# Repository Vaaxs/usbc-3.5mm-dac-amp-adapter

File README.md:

# usbc-3.5mm-dac-amp-adapter
Project for Stasis, a DAC amp that is also an adapter, to go from USB-C to 3.5mm.

## How it works

USB-C in → PCM2704CDB DAC → 3.5mm TRS out. The chip enumerates as a standard USB Audio Class device, so there is no firmware or drivers needed.

Specs

| Parameter | Value |
|---|---|
| DAC IC | Texas Instruments PCM2704CDB |
| Package | SSOP-28, 0.65mm pitch |
| USB | Full-speed USB 2.0 via USB-C receptacle |
| Output | 3.5mm TRS (stereo, no mic) |
| Sample rate | Up to 48 kHz, 16-bit |
| Crystal | 12 MHz ABM8-12.000MHZ-12-B1U-T |
| Power | Bus-powered from USB (500mA max) |
| Protection | 500mA polyfuse on VBUS |
| Board size | ~72mm × 22mm |
| Mounting | Two M2 mounting holes |

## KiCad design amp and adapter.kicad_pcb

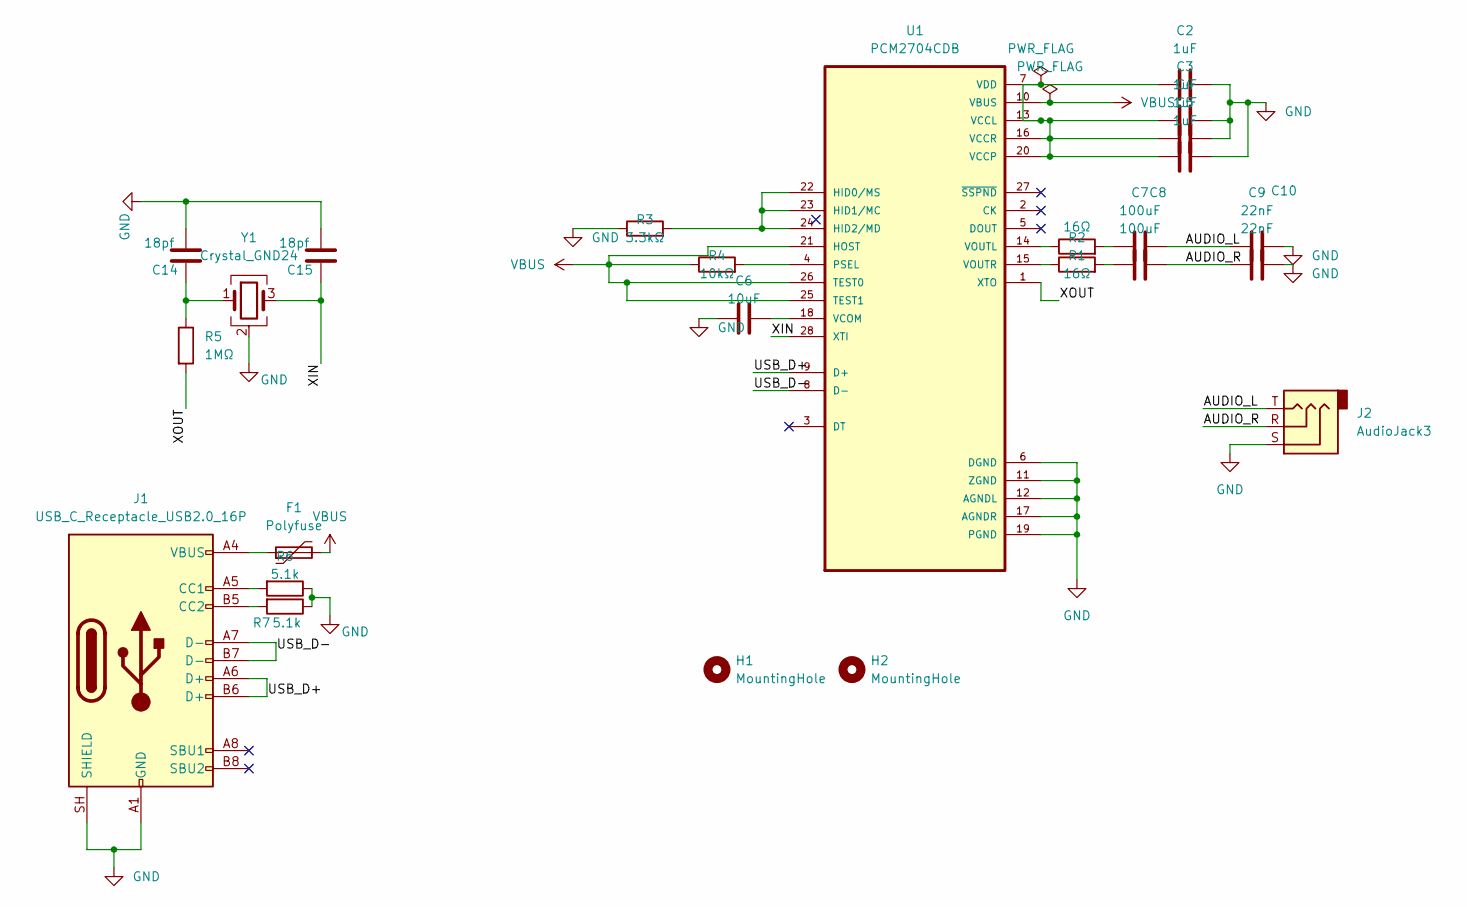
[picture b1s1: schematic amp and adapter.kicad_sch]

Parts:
C2, C3, C4, C5: 1uF; C_0402_1005Metric; LCSC Part # C52923
C6: 10uF; C_0805_2012Metric; LCSC Part # C15850
C7, C8: 100uF; C_1210_3225Metric; LCSC Part # C15008
C9, C10: 22nF; C_0402_1005Metric; LCSC Part # C1534
C14, C15: 18pf; C_0402_1005Metric; LCSC Part # C1548
F1: Polyfuse; Fuse_0805_2012Metric; LCSC Part # C70077
H1, H2: MountingHole; MountingHole_2.2mm_M2
J1: USB_C_Receptacle_USB2.0_16P; USB_C_Receptacle_HRO_TYPE-C-31-M-12; LCSC Part # C165948
J2: AudioJack3; Jack_3.5mm_CUI_SJ-3523-SMT_Horizontal; LCSC Part # C4991872
R1, R2: 16Ω; R_0402_1005Metric; LCSC Part # C25095
R3: 3.3kΩ; R_0402_1005Metric; LCSC Part # C25890
R4: 10kΩ; R_0402_1005Metric; LCSC Part # C25744
R5: 1MΩ; R_0402_1005Metric; LCSC Part # C26083
R6, R7: 5.1k; R_0402_1005Metric
U1: PCM2704CDB; SOP65P780X200-28N; LCSC Part # C5964
Y1: Crystal_GND24; Crystal_SMD_3225-4Pin_3.2x2.5mm; LCSC Part # C9002

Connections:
/AUDIO_L: C7.2, C9.2, J2.T
/AUDIO_R: C8.2, C10.2, J2.R
/USB_D+: J1.A6 (D+), J1.B6 (D+), U1.9 (D+)
/USB_D-: J1.A7 (D-), J1.B7 (D-), U1.8 (D-)
/XIN: C15.1, U1.28 (XTI), Y1.3
/XOUT: R5.2, U1.1 (XTO)
GND: C2.2, C3.2, C4.2, C5.2, C6.1, C9.1, C10.1, C14.2, C15.2, J1.A1 (GND), J1.A12 (GND), J1.B1 (GND), J1.B12 (GND), J1.SH (SHIELD), J2.S, R3.1, R6.1, R7.1, U1.6 (DGND), U1.11 (ZGND), U1.12 (AGNDL), U1.17 (AGNDR), U1.19 (PGND), Y1.2 (G), Y1.4 (G)
unnamed: C7.1, R2.2
unnamed: C8.1, R1.2
unnamed: C14.1, R5.1, Y1.1
unnamed: F1.1, J1.A4 (VBUS), J1.A9 (VBUS), J1.B4 (VBUS), J1.B9 (VBUS)
unnamed: J1.A5 (CC1), R6.2
unnamed: J1.B5 (CC2), R7.2
unnamed: R3.2, U1.22 (HID0/MS), U1.23 (HID1/MC), U1.24 (HID2/MD)
unnamed: R4.2, U1.4 (PSEL)
unnamed: C2.1, C3.1, C4.1, C5.1, U1.7 (VDD), U1.13 (VCCL), U1.16 (VCCR), U1.20 (VCCP)
unnamed: C6.2, U1.18 (VCOM)
unnamed: R2.1, U1.14 (VOUTL)
unnamed: R1.1, U1.15 (VOUTR)

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
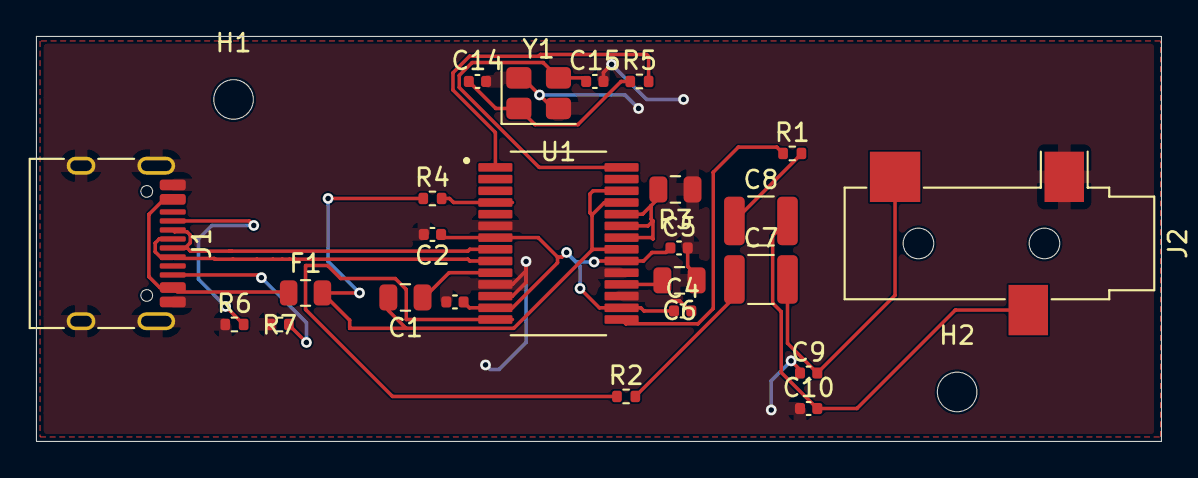
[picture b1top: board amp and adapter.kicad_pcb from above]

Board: 2 copper layers, 62.5 x 22.5 mm, 26 parts (0 on the bottom side), 21 nets.

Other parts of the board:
C1: 10uF; C_0805_2012Metric

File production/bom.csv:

Designator,Footprint,Quantity,Value,LCSC Part #
"C1, C6",0805,2,10uF,
"C10, C9",0402,2,22nF,
"C14, C15",0402,2,18pf,
"C2, C3, C4, C5",0402,4,1uF,
"C7, C8",1210,2,100uF,
F1,0805,1,Polyfuse,
J1,USB_C_Receptacle_HRO_TYPE-C-31-M-12,1,USB_C_Receptacle_USB2.0_16P,
J2,Jack_3.5mm_CUI_SJ-3523-SMT_Horizontal,1,AudioJack3,
"R1, R2",0402,2,16Ω,
R3,0805,1,3.3kΩ,
R4,0402,1,10kΩ,
R5,0402,1,1MΩ,
"R6, R7",0402,2,5.1k,
U1,SOP65P780X200-28N,1,PCM2704CDB,
Y1,Crystal_SMD_3225-4Pin_3.2x2.5mm,1,Crystal_GND24,
